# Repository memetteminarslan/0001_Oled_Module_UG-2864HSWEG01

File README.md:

# 0001_Oled_Module_UG-2864HSWEG01

You are seeing a large number of widely used OLED modules in electronic development kits. More information coming soon...

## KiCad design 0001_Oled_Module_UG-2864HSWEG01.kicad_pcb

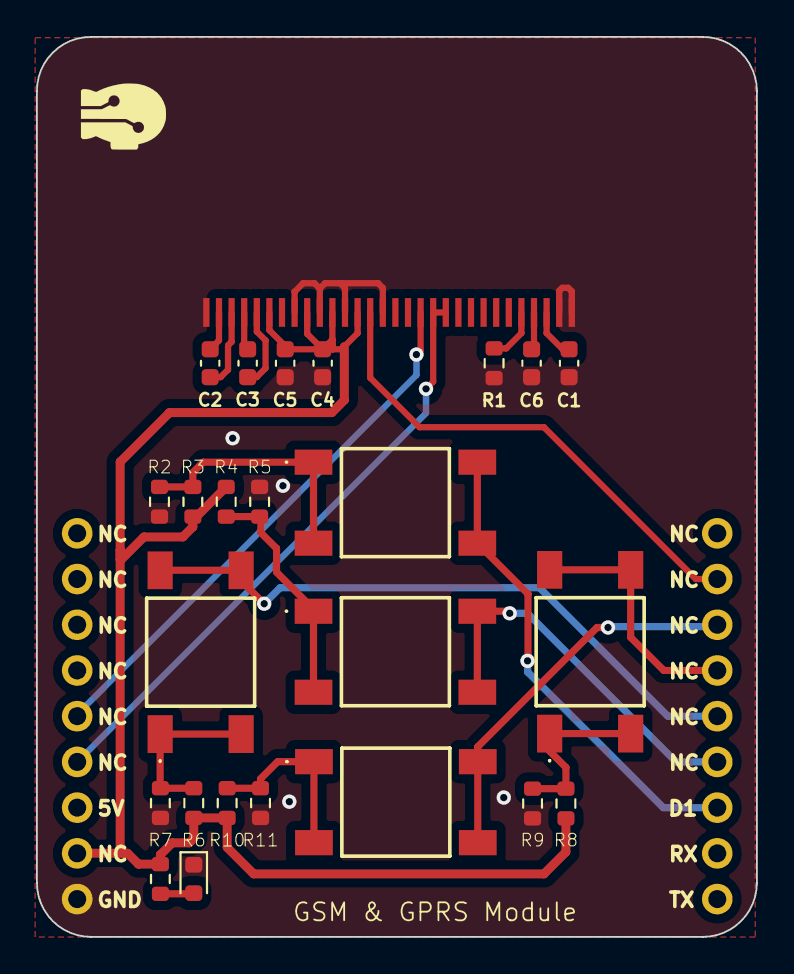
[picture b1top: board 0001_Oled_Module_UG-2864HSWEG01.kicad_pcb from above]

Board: 2 copper layers, 40.0 x 50.0 mm, 26 parts (0 on the bottom side), 23 nets.

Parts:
C1, C4, C5: 10uF; C_0603_1608Metric
C2, C3, C6: 2.2uF; C_0603_1608Metric
D1: LED; LED_0603_1608Metric
R1: 390k; R_0603_1608Metric
R2, R3, R4, R5, R6, R7, R8, R9, R10, R11: 0r; R_0603_1608Metric
R12: 470r; R_0603_1608Metric
SW1, SW2, SW3, SW4, SW5: SW_MEC_5E; TS046665BK160SMT
U1: UG-2864HSWEG01; 1X30-0.7MM
U3: air__module

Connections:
+3V3: C4.1, C5.1, R3.1, R4.1, R6.1, R8.1, R10.1, R12.1, U1.6 (VBAT), U1.9 (VDD), U1.11 (BS1), U1.13 (/CS), U3.8 (3V3)
GND: C1.2, C4.2, C5.2, C6.2, D1.1 (K), R1.1, R2.1, R5.1, R7.1, R9.1, R11.1, U1.1 (MT), U1.8 (VSS), U1.10 (BS0), U1.12 (BS2), U1.15 (D/C), U1.29 (VLSS), U1.30 (MT2), U3.9 (GND)
GPIO_01: SW1.3 (K), SW1.4 (A), U3.12 (GPIO)
GPIO_02: SW2.3 (K), SW2.4 (A), U3.13 (GPIO)
GPIO_03: SW3.3 (K), SW3.4 (A), U3.14 (GPIO)
GPIO_04: SW4.3 (K), SW4.4 (A), U3.15 (GPIO)
GPIO_05: SW5.3 (K), SW5.4 (A), U3.16 (GPIO)
unnamed: D1.2 (A), R12.2
unnamed: R2.2, R3.2, SW1.1, SW1.2
unnamed: R4.2, R5.2, SW2.1, SW2.2
unnamed: R6.2, R7.2, SW3.1, SW3.2
unnamed: R8.2, R9.2, SW4.1, SW4.2
unnamed: R10.2, R11.2, SW5.1, SW5.2
unnamed: C3.2, U1.5 (C1N)
unnamed: C3.1, U1.4 (C1P)
unnamed: C2.2, U1.3 (C2N)
unnamed: C2.1, U1.2 (C2P)
unnamed: R1.2, U1.26 (IREF)
unnamed: C1.1, U1.28 (VCC)
unnamed: C6.1, U1.27 (VCOMH)
RST: U1.14 (/RES), U3.17 (GPIO)
SCL: U1.18 (D0/DI), U3.5 (SCL)
SDA: U1.19 (D1/SCLK), U1.20 (D2), U3.6 (SDA)
